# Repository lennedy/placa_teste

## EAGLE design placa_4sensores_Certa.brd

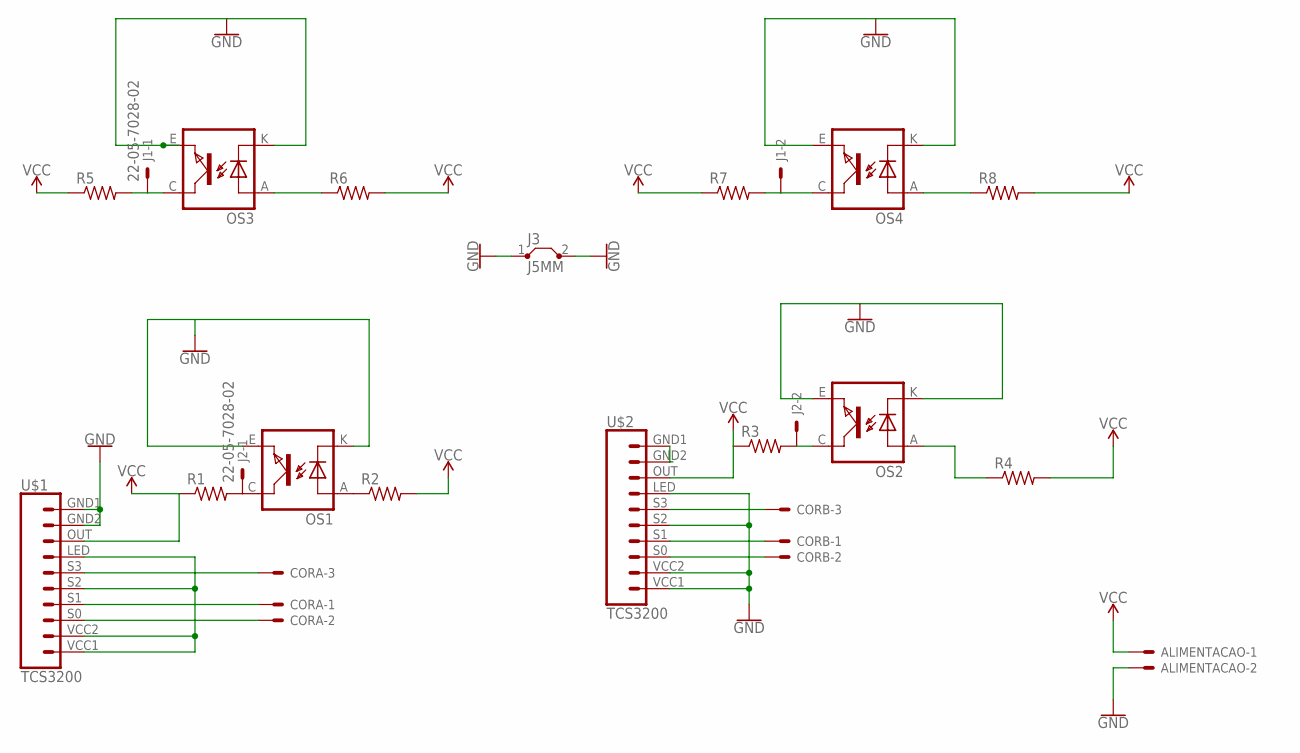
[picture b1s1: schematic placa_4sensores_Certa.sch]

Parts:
ALIMENTACAO: 22-05-7028-02; 7395-02
CORA: 22-05-7038-03; 7395-03
CORB: 22-05-7038-03; 7395-03
J1, J2: 22-05-7028-02; 7395-02
J3: J5MM; 05
OS1, OS2, OS3, OS4: TCRT5000
R1, R2, R3, R4, R5, R6, R7, R8: R-US_0204/5; 0204/5
U$1, U$2: TCS3200

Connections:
GND: ALIMENTACAO.2, J3.1, J3.2, OS1.E (EMITTER), OS1.K (CATHODE), OS2.E (EMITTER), OS2.K (CATHODE), OS3.E (EMITTER), OS3.K (CATHODE), OS4.E (EMITTER), OS4.K (CATHODE), U$1.GND1, U$1.GND2, U$2.LED, U$2.S2, U$2.VCC1, U$2.VCC2
unnamed: CORA.2, U$1.S0
unnamed: CORB.1, U$2.S1
unnamed: CORB.2, U$2.S0
unnamed: CORA.3, U$1.S3
unnamed: CORA.1, U$1.S1
unnamed: CORB.3, U$2.S3
unnamed: OS1.A (ANODE), R2.1
unnamed: J2.1, OS1.C (COLLECTOR), R1.2
unnamed: J2.2, OS2.C (COLLECTOR), R3.2
unnamed: U$1.LED, U$1.S2, U$1.VCC1, U$1.VCC2
unnamed: OS2.A (ANODE), R4.1
unnamed: OS3.A (ANODE), R6.1
unnamed: J1.1, OS3.C (COLLECTOR), R5.2
unnamed: J1.2, OS4.C (COLLECTOR), R7.2
unnamed: OS4.A (ANODE), R8.1
VCC: ALIMENTACAO.1, R1.1, R2.2, R3.1, R4.2, R5.1, R6.2, R7.1, R8.2, U$1.OUT, U$2.OUT

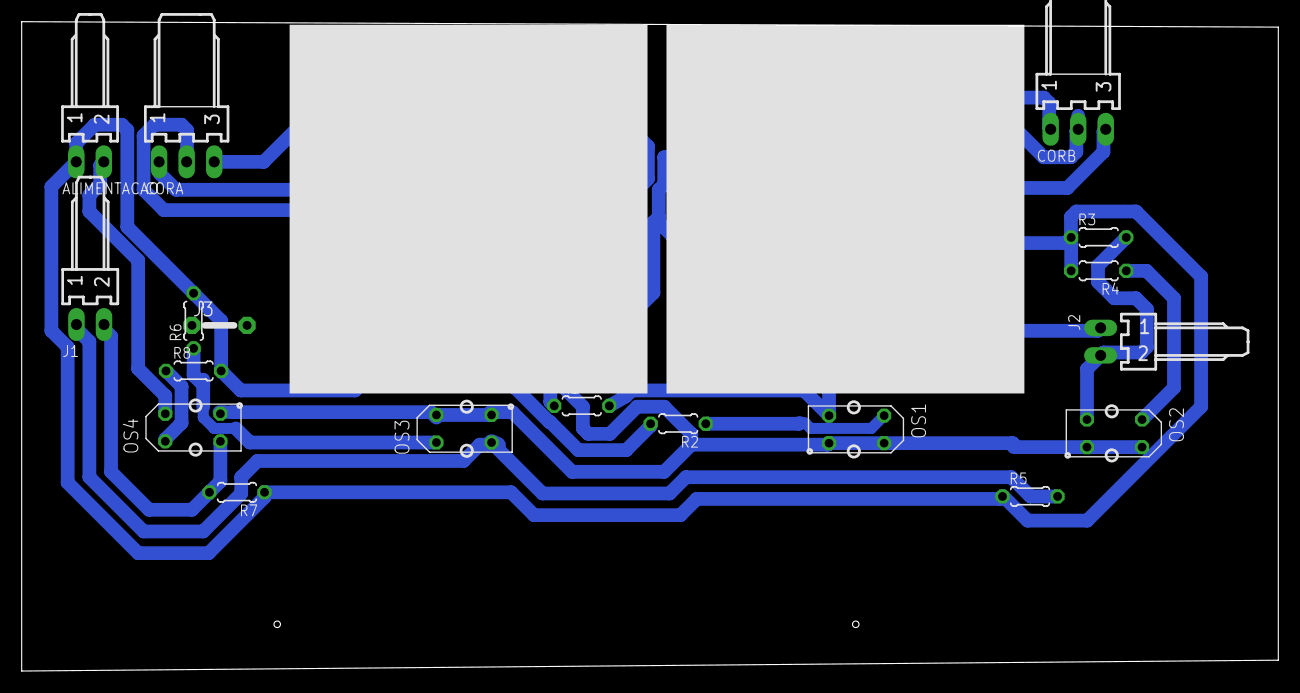
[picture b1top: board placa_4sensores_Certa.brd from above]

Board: 2 copper layers, 115.9 x 59.9 mm, 20 parts (0 on the bottom side), 17 nets.

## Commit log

2017-07-29 placa incial

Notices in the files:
parts and their libraries:
Robotica-IFRN-SC: Licensing: Creative Commons ShareAlike 4.0 International - https://creativecommons.org/licenses/by-sa/4.0
